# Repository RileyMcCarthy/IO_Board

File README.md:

# IO Board

The IO board is an extension for the Mad Board to maintain an isolated connection to the tensile testing machine.

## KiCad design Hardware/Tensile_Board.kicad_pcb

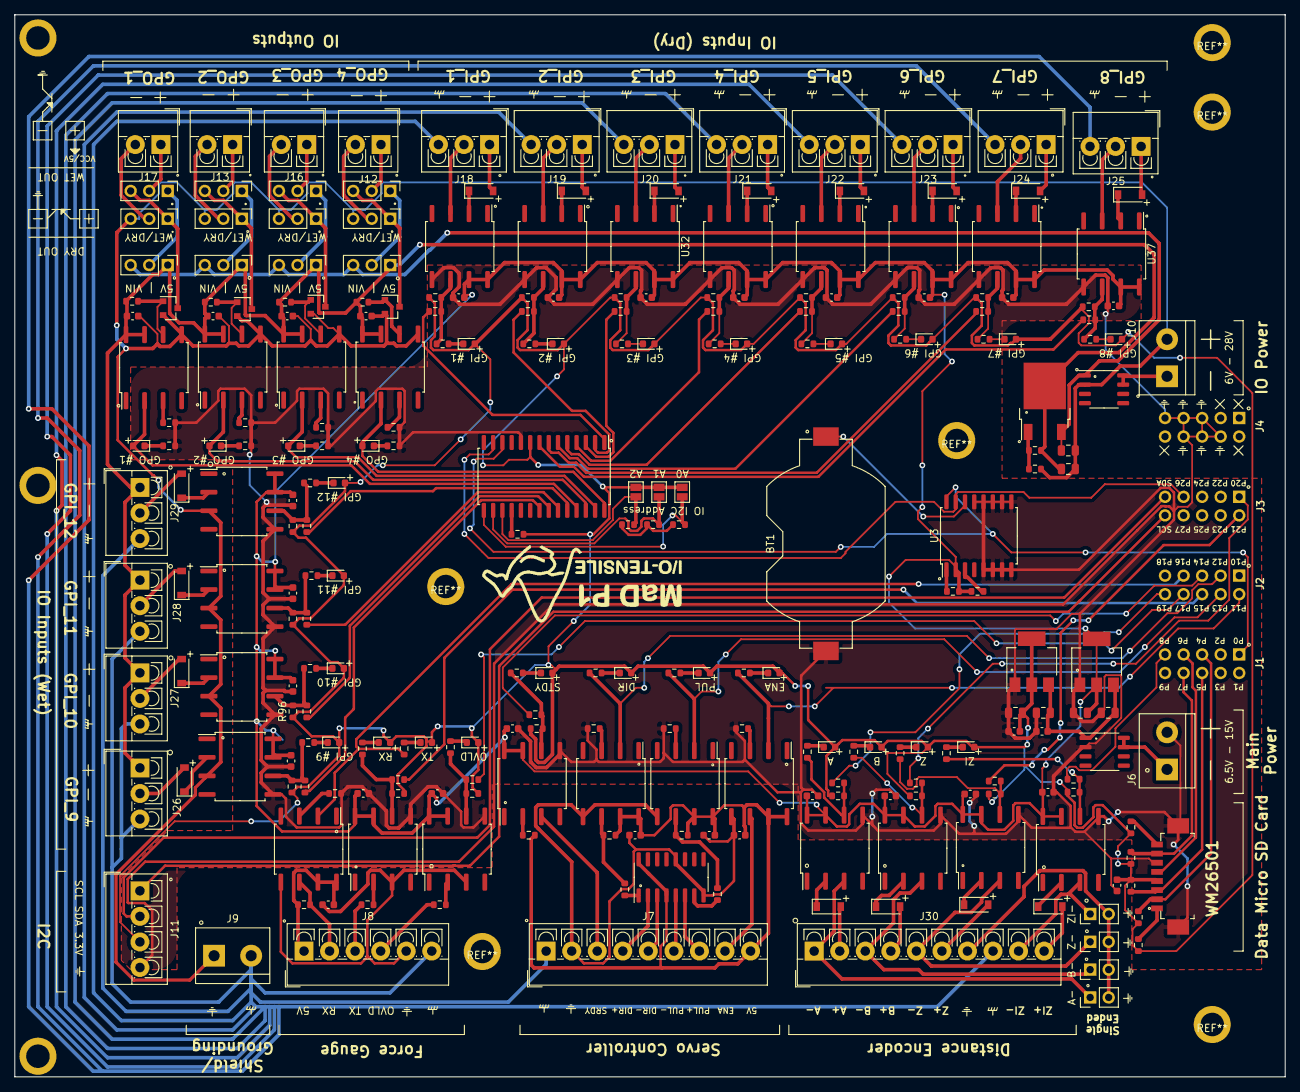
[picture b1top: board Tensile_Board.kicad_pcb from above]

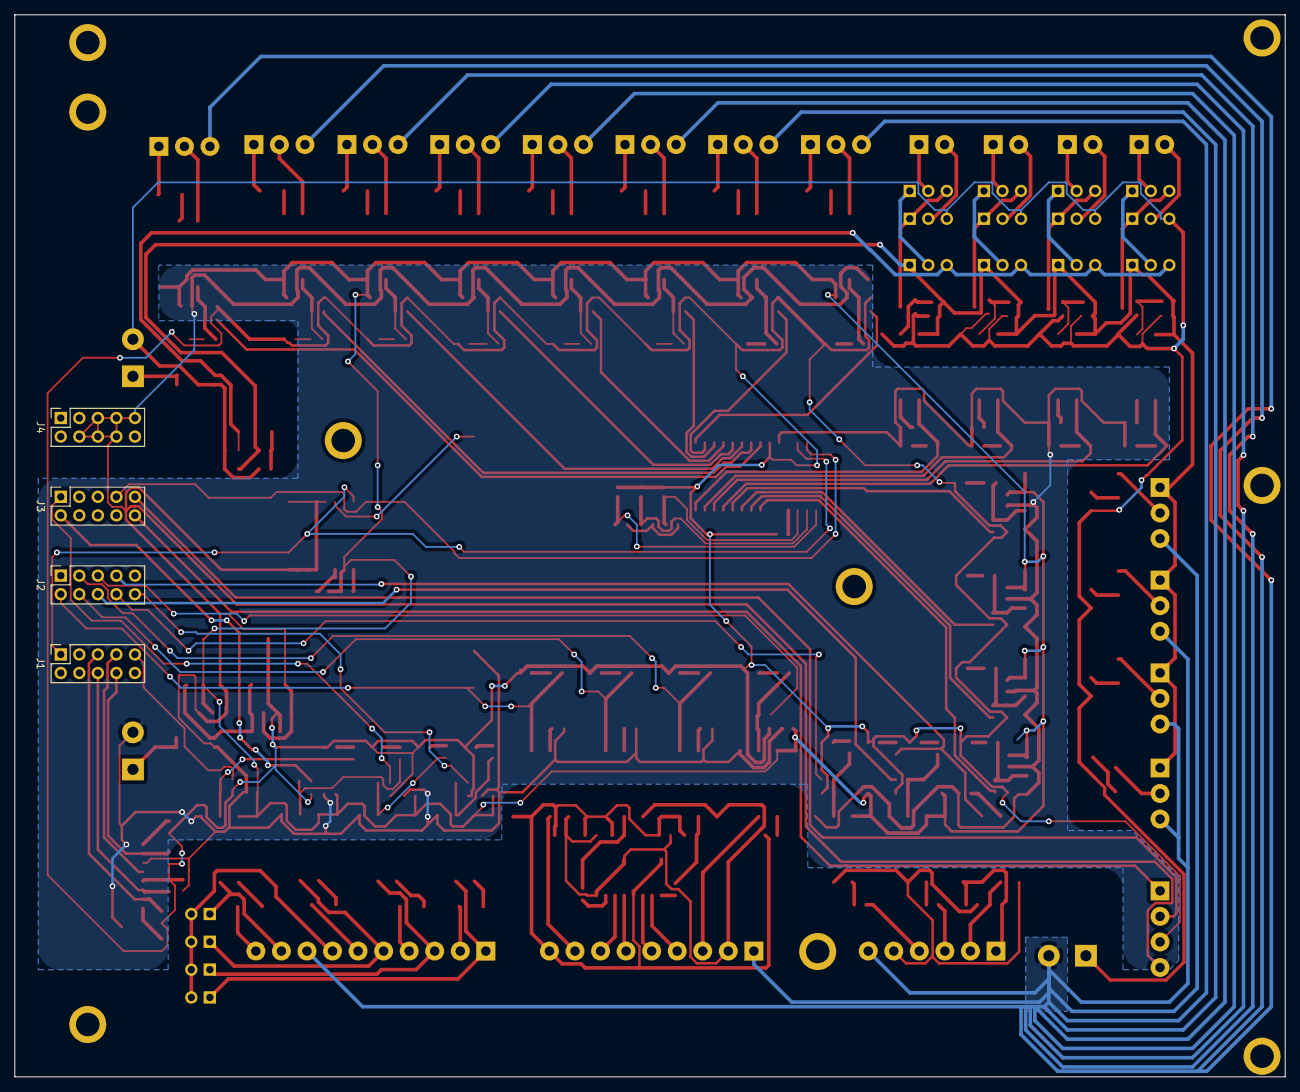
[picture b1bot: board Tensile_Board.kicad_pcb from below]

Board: 2 copper layers, 174.0 x 145.5 mm, 268 parts (4 on the bottom side), 195 nets.

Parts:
BT1: CR2032; BatteryHolder_Keystone_1058_1x2032
C1, C8, C9, C12, C13, C14, C15, C16, C17, C18, C19, C20, C23, C24, C25, C26, C27, C28, C29, C30, C31, C32, C33, C34, C35, C36, C37, C38: 0.1uF; C_0603_1608Metric
C2, C3: 10uF; C_0805_2012Metric
C4, C6: 4.7uF; C_0805_2012Metric
C5, C7: 1uF; C_0603_1608Metric
C21: 0.1uF; C_0805_2012Metric
C22: 1uF; C_0805_2012Metric
D1, D2, D4, D5, D6, D7, D8, D9, D10, D11, D12, D13, D14, D15, D16, D17, D18, D19, D20, D21, D22, D23, D24, D25, D26, D27: BLUE; LED_0603_1608Metric
D3: LED; LED_0603_1608Metric
DISP_HOLE_1, DISP_HOLE_2, DISP_HOLE_3: Hole_5.08
J1, J2, J3, J4: Conn_02x05_Odd_Even; PinSocket_2x05_P2.54mm_Vertical
J5: Micro_SD_Card; WM26501
J6: Main_Power; TerminalBlock_bornier-2_P5.08mm
J7: Screw_Terminal_01x09; TerminalBlock_4Ucon_1x09_P3.50mm_Vertical
J8: Screw_Terminal_01x06; TerminalBlock_4Ucon_1x06_P3.50mm_Vertical
J9: Grounding; TerminalBlock_bornier-2_P5.08mm
J10: IO_Power; TerminalBlock_bornier-2_P5.08mm
J11: Screw_Terminal_01x04; TerminalBlock_4Ucon_1x04_P3.50mm_Vertical
J12, J13, J16, J17: Screw_Terminal_01x02; TerminalBlock_4Ucon_1x02_P3.50mm_Vertical
J18, J19, J20, J21, J22, J23, J24, J25, J26, J27, J28, J29: Screw_Terminal_01x03; TerminalBlock_4Ucon_1x03_P3.50mm_Vertical
J30: Screw_Terminal_01x10; TerminalBlock_4Ucon_1x10_P3.50mm_Vertical
JP1: A2; SolderJumper-2_P1.3mm_Open_Pad1.0x1.5mm
JP2: A1; SolderJumper-2_P1.3mm_Open_Pad1.0x1.5mm
JP3: A0; SolderJumper-2_P1.3mm_Open_Pad1.0x1.5mm
JP4, JP5, JP6, JP7: Jumper_2_Open; PinHeader_1x02_P2.54mm_Vertical
JP10, JP11, JP12, JP13, JP15, JP16, JP18, JP19, JP21, JP22, JP24, JP25: Jumper_3_Open; PinHeader_1x03_P2.54mm_Vertical
LOGO: LOGO_1
Q3, Q4, Q5, Q6, Q7, Q8, Q9, Q10, Q11, Q12, Q13, Q14, Q15, Q16, Q17, Q18: NSI50010Y; D_SOD-123
R1, R2, R3, R4, R5: 100K; R_0603_1608Metric
R6, R7: 4.7K; R_0603_1608Metric
R8, R9, R17, R24, R25, R26, R27, R28, R29, R38, R39, R40, R41, R56, R57, R58, R59, R60, R61, R68, R69, R70, R71, R72, R73: 10K; R_0603_1608Metric
R10, R11, R18: 360R; R_0603_1608Metric
R12, R19, R20: 470R; R_0603_1608Metric
R13, R14, R15, R21, R42, R43, R44, R45: 270R; R_0603_1608Metric
R16, R32, R33, R34, R35: 620R; R_0603_1608Metric
R22, R23: 330R; R_0603_1608Metric
R30, R31, R36, R37, R50, R51, R52, R53, R54, R55, R62, R63, R64, R65, R66, R67, R77, R78, R79, R80, R81, R82, R83, R84, R85, R86: 100R; R_0603_1608Metric
R46, R47, R48, R49, R87, R88, R89, R90, R91, R92, R93, R94, R95, R96, R97, R98: 1K; R_0603_1608Metric
R74: 680R; R_0603_1608Metric
R75: 220R; R_0603_1608Metric
R76: 33R; R_0603_1608Metric
U1: AMS1117-5.0; SOT-223-3_TabPin2
U2: AMS1117-3.3; SOT-223-3_TabPin2
U3: DS3231M; SOIC-16W_7.5x10.3mm_P1.27mm
U4: AM26LS31CDR; SOIC-16_3.9x9.9mm_P1.27mm
U5, U6, U7, U8, U9, U10, U11, U15, U16, U17, U18, U22, U23, U24, U25, U30, U31, U32, U33, U34, U35, U36, U37, U38, U39, U40, U41: 6N137; SOP-8_6.62x9.15mm_P2.54mm
U12: MCP23017_SO; SOIC-28W_7.5x17.9mm_P1.27mm
U13, U20: APM4953; SOP-8_3.9x4.9mm_P1.27mm
U21: LM317_TO-252; TO-252-2
U26, U27, U28, U29: NUD3124; SOT-23

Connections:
5V_IO: C22.1, C23.1, C24.1, C25.1, C26.1, J26.1, J27.1, J28.1, J29.1, JP10.1, JP11.1, JP12.1, JP13.1, R46.1, R47.1, R48.1, R49.1, R75.1, U21.2, U22.7, U22.8, U23.7, U23.8, U24.7, U24.8, U25.7, U25.8
+3V3_TS: C1.1, C6.1, C7.1, D1.2, D2.2, D7.2, D8.2, D9.2, D10.2, D11.2, D12.2, D13.2, D14.2, D15.2, D16.2, D17.2, D18.2, D19.2, D20.2, D21.2, D22.2, D23.2, D24.2, D25.2, D26.2, D27.2, J5.4, J11.3, JP1.1, JP2.1, JP3.1, R1.1, R2.1, R3.1, R4.1, R5.1, R16.1, R22.1, R23.1, R28.1, R32.1, R33.1, R34.1, R35.1, R87.1, R88.1, R89.1, R90.1, R91.1, R92.1, R93.1, R94.1, R95.1, R96.1, R97.1, R98.1, U2.2, U12.9
+5V_FG: C18.1, J8.1, R18.1, U9.7, U9.8
+5V_SC: C8.1, C9.1, C16.1, J7.9, R10.1, R11.1, R12.1, U4.4, U4.16, U5.7, U5.8, U6.7, U6.8, U7.7, U7.8
+5V_TS: C3.1, C12.1, C13.1, C14.1, C15.1, C17.1, C19.1, C20.1, C27.1, C28.1, C29.1, C30.1, C31.1, C32.1, C33.1, C34.1, C35.1, C36.1, C37.1, C38.1, R6.1, R7.1, U1.2, U3.2, U8.7, U8.8, U10.7, U10.8, U11.7, U11.8, U15.7, U15.8, U16.7, U16.8, U17.7, U17.8, U18.7, U18.8, U30.7, U30.8, U31.7, U31.8, U32.7, U32.8, U33.7, U33.8, U34.7, U34.8, U35.7, U35.8, U36.7, U36.8, U37.7, U37.8, U38.7, U38.8, U39.7, U39.8, U40.7, U40.8, U41.7, U41.8
DIR: R8.1, U4.1
DIR+: J7.4, U4.2
DIR-: J7.5, U4.3
ENA: J7.8, U6.6
FG_OVLD: J8.4, R19.1
FG_RX: J8.2, R18.2, U9.6
FG_TX: J8.3, R20.1
GND: R26.2, R27.2, R29.2
GND_ENC: J30.7, JP4.2, JP5.2, JP6.2, JP7.2
GND_FG: C18.2, J8.5, U9.5, U10.3, U11.3
GND_IO: C21.2, C22.2, C23.2, C24.2, C25.2, C26.2, J9.1, J10.2, JP16.3, JP19.3, JP22.3, JP25.3, R74.2, U13.2, U22.5, U23.5, U24.5, U25.5, U26.2, U27.2, U28.2, U29.2, U38.3, U39.3, U40.3, U41.3
GND_SC: C8.2, C9.2, C16.2, J7.2, U4.8, U4.12, U5.5, U6.5, U7.5
GND_TSD: BT1.2, C1.2, C2.2, C3.2, C4.2, C5.2, C6.2, C7.2, C12.2, C13.2, C14.2, C15.2, C17.2, C19.2, C20.2, C27.2, C28.2, C29.2, C30.2, C31.2, C32.2, C33.2, C34.2, C35.2, C36.2, C37.2, C38.2, J4.4, J4.5, J4.6, J4.7, J4.8, J4.9, J5.6, J5.9, J6.2, J11.4, R13.2, R14.2, R15.2, R21.2, R42.2, R43.2, R44.2, R45.2, R76.2, R77.2, R78.2, R79.2, U1.1, U2.1, U3.5, U3.6, U3.7, U3.8, U3.9, U3.10, U3.11, U3.12, U3.13, U8.5, U10.5, U11.5, U12.10, U15.5, U16.5, U17.5, U18.5, U20.2, U30.5, U31.5, U32.5, U33.5, U34.5, U35.5, U36.5, U37.5, U38.5, U39.5, U40.5, U41.5
GPA0: R70.1, U12.21
GPA1: R71.1, U12.22
GPA2: R72.1, U12.23
GPA3: R73.1, U12.24
GPA4: D6.2, U12.25, U25.2
GPA5: D4.2, U12.26, U23.2
GPA6: D5.2, U12.27, U24.2
GPA7: D3.2, U12.28, U22.2
GPB0: R56.1, U12.1
GPB1: R57.1, U12.2
GPB2: R58.1, U12.3
GPB3: R59.1, U12.4
GPB4: R60.1, U12.5
GPB5: R61.1, U12.6
GPB6: R68.1, U12.7
GPB7: R69.1, U12.8
GPI_1+: J18.1, Q7.2
GPI_1-: J18.2, U30.3
GPI_2+: J19.1, Q8.2
GPI_2-: J19.2, U31.3
GPI_3+: J20.1, Q9.2
GPI_3-: J20.2, U32.3
GPI_4+: J21.1, Q10.2
GPI_4-: J21.2, U33.3
GPI_5+: J22.1, Q11.2
GPI_5-: J22.2, U34.3
GPI_6+: J23.1, Q12.2
GPI_6-: J23.2, U35.3
GPI_7+: J24.1, Q13.2
GPI_7-: J24.2, U36.3
GPI_8+: J25.1, Q14.2
GPI_8-: J25.2, U37.3
GPI_9: J26.2, Q15.2
GPI_10: J27.2, Q16.2
GPI_11: J28.2, Q17.2
GPI_12: J29.2, Q18.2
GPO_1+: J17.1, JP24.2
GPO_1-: J17.2, JP25.2
GPO_2+: J13.1, JP18.2
GPO_2-: J13.2, JP19.2
GPO_3+: J16.1, JP21.2
GPO_3-: J16.2, JP22.2
GPO_4+: J12.1, JP15.2
GPO_4-: J12.2, JP16.2
GPO_D1: JP24.3, JP25.1, U29.3
GPO_D2: JP18.3, JP19.1, U27.3
GPO_D3: JP21.3, JP22.1, U28.3
GPO_D4: JP15.3, JP16.1, U26.3
unnamed: BT1.1, U3.14
unnamed: D1.1, R50.1
unnamed: D2.1, R30.1
unnamed: D3.1, R76.1
unnamed: D4.1, R77.1
unnamed: D5.1, R78.1
unnamed: D6.1, R79.1
unnamed: D7.1, R51.1
unnamed: D8.1, R52.1
unnamed: D9.1, R53.1
unnamed: D10.1, R54.1
unnamed: D11.1, R55.1
unnamed: D12.1, R62.1
unnamed: D13.1, R63.1
unnamed: D14.1, R64.1
unnamed: D15.1, R65.1
unnamed: D16.1, R66.1
unnamed: D17.1, R67.1
unnamed: D18.1, R31.1
unnamed: D19.1, R36.1
unnamed: D20.1, R37.1
unnamed: D21.1, R80.1
unnamed: D22.1, R81.1
unnamed: D23.1, R82.1
unnamed: D24.1, R83.1
unnamed: D25.1, R84.1
unnamed: D26.1, R85.1
unnamed: D27.1, R86.1
unnamed: J5.1, R5.2
unnamed: J5.8, R1.2
unnamed: J6.1, U20.7, U20.8
unnamed: J10.1, U13.7, U13.8
unnamed: JP1.2, R26.1, U12.17
unnamed: JP2.2, R27.1, U12.16
unnamed: JP3.2, R29.1, U12.15
unnamed: Q3.1, U15.2
unnamed: Q4.1, U16.2
unnamed: Q5.1, U17.2
unnamed: Q6.1, U18.2
unnamed: Q7.1, U30.2
unnamed: Q8.1, U31.2
unnamed: Q9.1, U32.2
unnamed: Q10.1, U33.2
unnamed: Q11.1, U34.2
unnamed: Q12.1, U35.2
unnamed: Q13.1, U36.2
unnamed: Q14.1, U37.2
unnamed: Q15.1, U38.2
unnamed: Q16.1, U39.2
unnamed: Q17.1, U40.2
unnamed: Q18.1, U41.2
unnamed: R6.2, U3.1
unnamed: R7.2, U3.3
unnamed: R8.2, R10.2, U5.6
unnamed: R9.2, R11.2, U7.6
unnamed: R12.2, U8.2
unnamed: R13.1, U5.3
unnamed: R14.1, U6.3
unnamed: R15.1, U7.3
unnamed: R16.2, R17.2, R37.2, U8.6
unnamed: R19.2, U10.2
unnamed: R20.2, U11.2
unnamed: R21.1, U9.3
unnamed: R22.2, R24.2, R81.2, U10.6
unnamed: R23.2, R25.2, R82.2, U11.6
unnamed: R28.2, U12.18
unnamed: R32.2, R38.2, R86.2, U15.6
unnamed: R33.2, R39.2, R85.2, U16.6
unnamed: R34.2, R40.2, R84.2, U17.6
unnamed: R35.2, R41.2, R83.2, U18.6
unnamed: R42.1, U22.3
unnamed: R43.1, U23.3
unnamed: R44.1, U24.3
unnamed: R45.1, U25.3
unnamed: R46.2, U22.6, U26.1
unnamed: R47.2, U23.6, U27.1
unnamed: R48.2, U24.6, U28.1
unnamed: R49.2, U25.6, U29.1
unnamed: R50.2, R56.2, R87.2, U30.6
unnamed: R51.2, R57.2, R88.2, U31.6
unnamed: R52.2, R58.2, R89.2, U32.6
unnamed: R53.2, R59.2, R90.2, U33.6
unnamed: R54.2, R60.2, R91.2, U34.6
unnamed: R55.2, R61.2, R92.2, U35.6
unnamed: R62.2, R68.2, R93.2, U36.6
unnamed: R63.2, R69.2, R94.2, U37.6
unnamed: R64.2, R70.2, R95.2, U38.6
unnamed: R65.2, R71.2, R96.2, U39.6
unnamed: R66.2, R72.2, R97.2, U40.6
unnamed: R67.2, R73.2, R98.2, U41.6
unnamed: R74.1, R75.2, U21.1
OUTA+: J30.2, Q6.2
OUTA-: J30.1, JP7.1, U18.3
OUTB+: J30.4, Q5.2
OUTB-: J30.3, JP6.1, U17.3
OUTZ+: J30.6, Q4.2
OUTZ-: J30.5, JP5.1, U16.3
OUTZI+: J30.10, Q3.2
OUTZI-: J30.9, JP4.1, U15.3
P0: J1.1, U3.16, U12.12
P4: J1.5, J5.2, R4.2
P5: J1.6, J5.3, R3.2
P6: J1.7, J5.5
P7: J1.8, J5.7, R2.2
P8: J1.9, R38.1
P11: J2.2, R31.2, U6.2
P12: J2.3, R30.2, U5.2
P13: J2.4, R36.2, U7.2
P14: J2.5, R17.1
P15: J2.6, R25.1
P16: J2.7, R80.2, U9.2
P17: J2.8, R24.1
P19: J2.10, R41.1
P20: J3.1, R40.1
P21: J3.2, R39.1
P26: J3.7, U3.15, U12.13
PUL: R9.1, U4.7
PUL+: J7.7, U4.6
PUL-: J7.6, U4.5
SCL: J3.10, J11.1
SDA: J3.9, J11.2
SHIELD: J7.1, J8.6, J9.2, J18.3, J19.3, J20.3, J21.3, J22.3, J23.3, J24.3, J25.3, J26.3, J27.3, J28.3, J29.3, J30.8
SRDY: J7.3, U8.3
VIN_IO: C21.1, JP10.3, JP11.3, JP12.3, JP13.3, U13.1, U21.3
V_GPO1: JP13.2, JP24.1
V_GPO2: JP11.2, JP18.1
V_GPO3: JP12.2, JP21.1
V_GPO4: JP10.2, JP15.1
V_IN: C2.1, C4.1, C5.1, U1.3, U2.3, U20.1

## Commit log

2021-02-23 reorganization of files
2021-04-02 fixed silk screen issues with rev_1
